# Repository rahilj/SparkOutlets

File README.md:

SparkOutlets
============

Spark controlled outlet switches
You'll need RF remote controlled outlet switches (http://www.amazon.com/dp/B00DQ2KGB2), optocouplers 
and Spark Core (spark.io) to control upto 5 outlets over the internet.
v_1 uses brute force hack
v_2 will be more elegant with a RF T emulating button press
More documentation on the project here:
https://community.spark.io/t/spark-controlled-outlet-switches/6283

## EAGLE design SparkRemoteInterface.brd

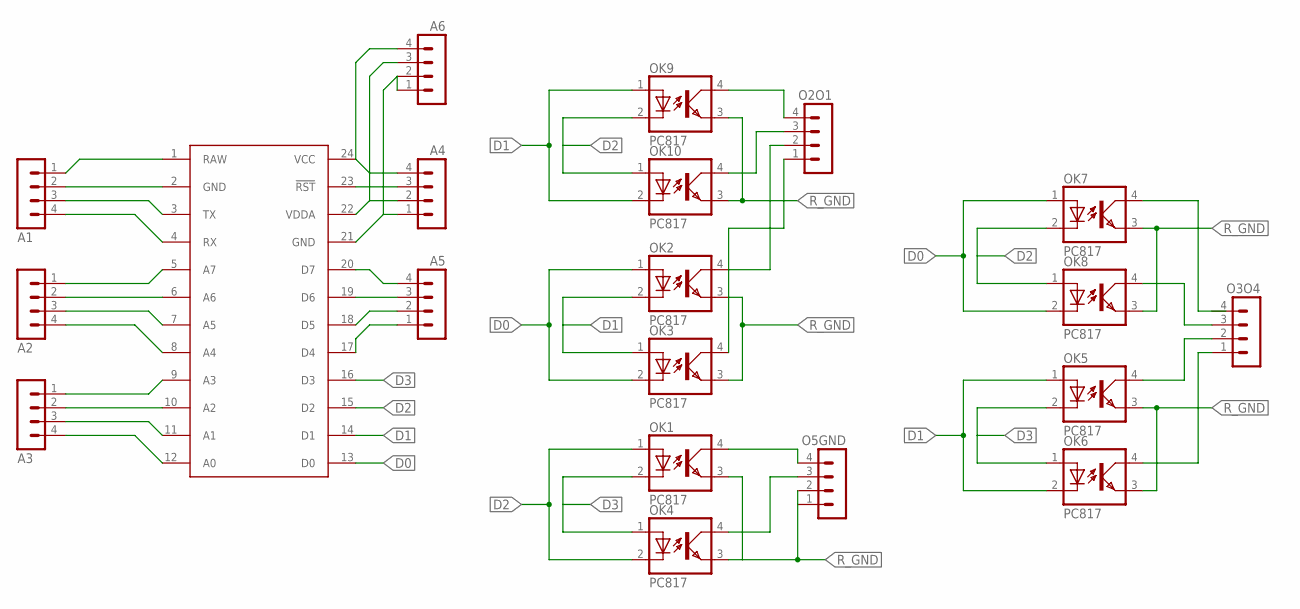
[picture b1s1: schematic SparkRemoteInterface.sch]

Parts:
A1, A2, A3, A4, A5, A6: MA04-1
O2O1, O3O4, O5GND: MA04-1
OK1, OK2, OK3, OK4, OK5, OK6, OK7, OK8, OK9, OK10: PC817; DIL04
U$1: SPARK_CORECORE; SPARK_CORE

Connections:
1R: O2O1.2, OK2.4 (COL)
1W: O2O1.1, OK3.4 (COL)
2R: O2O1.4, OK9.4 (COL)
2W: O2O1.3, OK10.4 (COL)
3R: OK7.4 (COL)
3W: O3O4.3, OK8.4 (COL)
4R: O3O4.2, OK5.4 (COL)
4W: O3O4.1, OK6.4 (COL)
5R: O5GND.4, OK1.4 (COL)
5W: O5GND.3, OK4.4 (COL)
D0: OK2.1 (A), OK3.2 (C), OK7.1 (A), OK8.2 (C), U$1.13 (D0)
D1: OK2.2 (C), OK3.1 (A), OK5.1 (A), OK6.2 (C), OK9.1 (A), OK10.2 (C), U$1.14 (D1)
D2: OK1.1 (A), OK4.2 (C), OK7.2 (C), OK8.1 (A), OK9.2 (C), OK10.1 (A), U$1.15 (D2)
D3: OK1.2 (C), OK4.1 (A), OK5.2 (C), OK6.1 (A), U$1.16 (D3)
unnamed: A1.1, U$1.1 (RAW)
unnamed: A3.1, U$1.9 (A3)
unnamed: A1.2, U$1.2 (GND)
unnamed: A1.3, U$1.3 (TX)
unnamed: A1.4, U$1.4 (RX)
unnamed: A2.1, U$1.5 (A7)
unnamed: A2.2, U$1.6 (A6)
unnamed: A2.3, U$1.7 (A5)
unnamed: A2.4, U$1.8 (A4)
unnamed: A3.2, U$1.10 (A2)
unnamed: A3.3, U$1.11 (A1)
unnamed: A3.4, U$1.12 (A0)
unnamed: A4.4, A6.4, U$1.24 (VCC)
unnamed: A4.3, U$1.23 (!RST)
unnamed: A4.2, A6.3, U$1.22 (VDDA)
unnamed: A4.1, A6.1, A6.2, U$1.21 (GND)
unnamed: A5.4, U$1.20 (D7)
unnamed: A5.3, U$1.19 (D6)
unnamed: A5.2, U$1.18 (D5)
unnamed: A5.1, U$1.17 (D4)
R_GND: O5GND.1, O5GND.2, OK1.3 (EMIT), OK2.3 (EMIT), OK3.3 (EMIT), OK4.3 (EMIT), OK5.3 (EMIT), OK6.3 (EMIT), OK7.3 (EMIT), OK8.3 (EMIT), OK9.3 (EMIT), OK10.3 (EMIT)

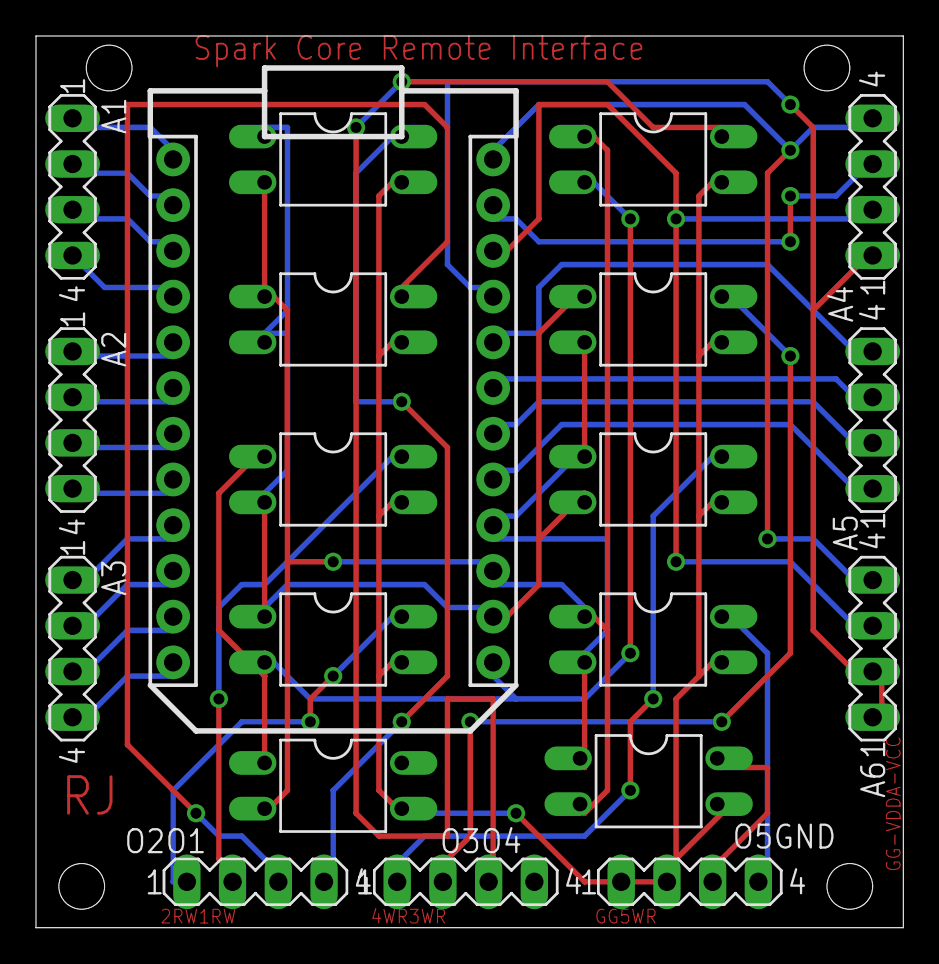
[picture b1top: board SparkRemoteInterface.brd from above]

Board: 2 copper layers, 48.2 x 49.5 mm, 20 parts (0 on the bottom side), 34 nets.

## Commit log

2014-08-25 Update SparkOutletSwitches.cpp
    Spark core firmware
2014-08-25 Create index.html
    webpage to toggle outlet states
    forked through spare remote app
2014-08-25 Create SparkRemoteInterface.brd
    Connection missing - 3R and OK8 or OK7
2014-08-25 Create SparkRemoteInterface.sch
    Schematic for Spark core and Remote interface
